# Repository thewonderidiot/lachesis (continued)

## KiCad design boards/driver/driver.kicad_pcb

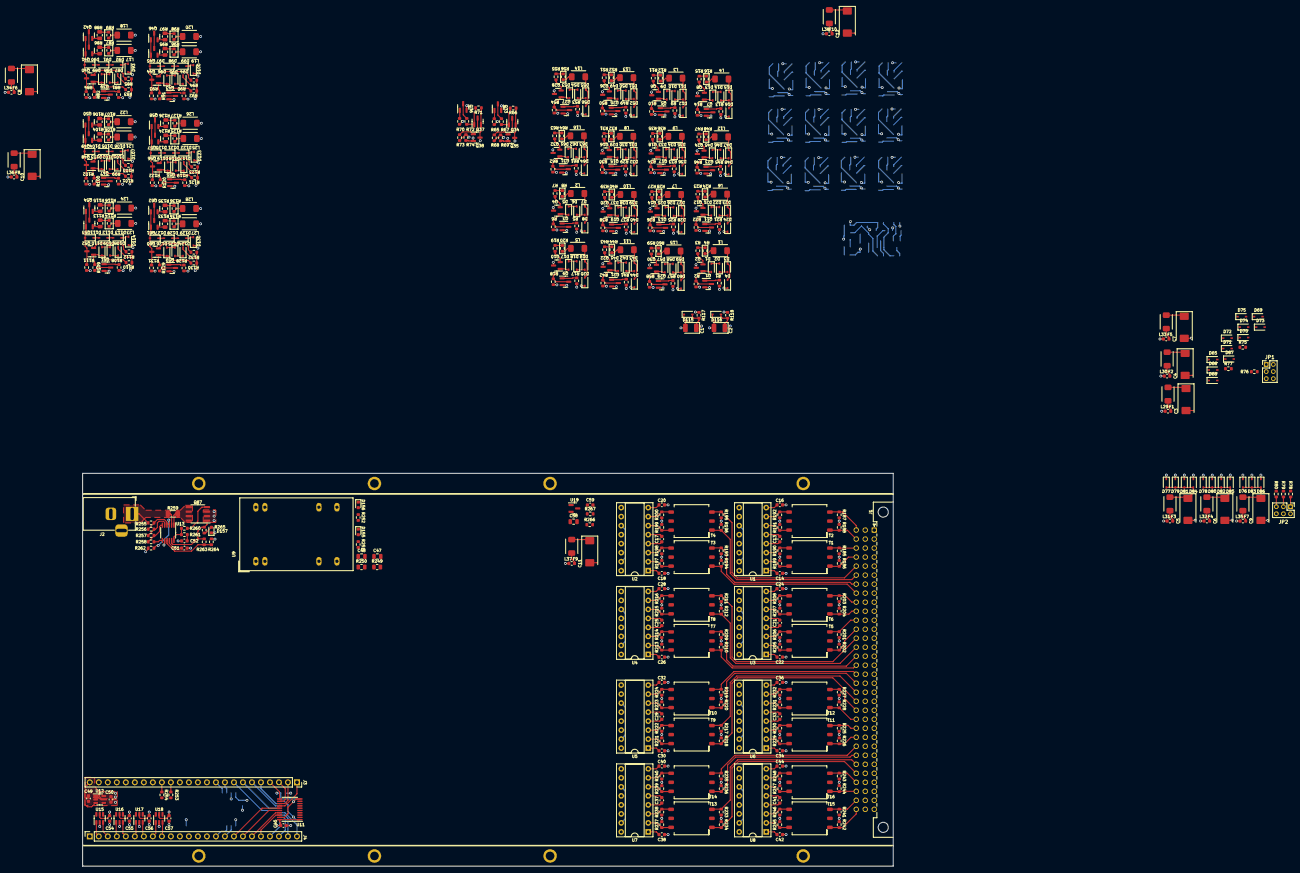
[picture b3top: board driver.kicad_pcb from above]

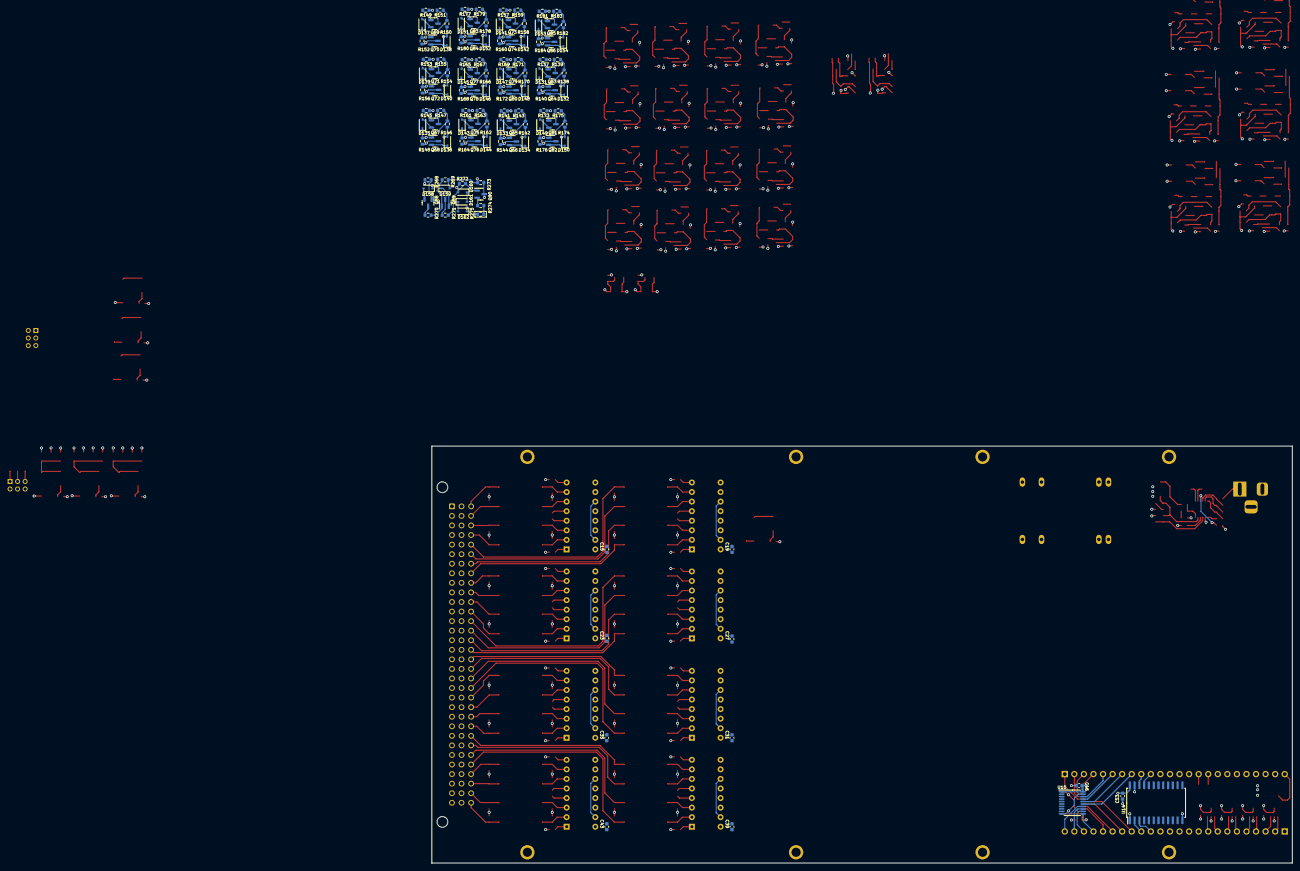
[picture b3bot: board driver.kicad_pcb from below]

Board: 6 copper layers, 228.6 x 110.7 mm, 683 parts (124 on the bottom side), 562 nets.

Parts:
C1, C2: 1.0uF; CP_EIA-3528-21_Kemet-B
C3, C4, C5, C6, C7, C8, C9, C10, C11, C12: 6.8uF; CP_EIA-7343-31_Kemet-D
C13, C15, C16, C17, C19, C20, C21, C23, C24, C25, C27, C28, C29, C31, C32, C33, C35, C36, C37, C39, C40, C41, C43, C44, C52: 0.01uF; C_0603_1608Metric
C14, C18, C22, C26, C30, C34, C38, C42, C51: 100pF; C_0603_1608Metric
C45, C46, C53, C54, C55, C56, C57: 0.1uF; C_0603_1608Metric
C47, C48: 1.0uF; C_0805_2012Metric
C49, C50, C59: 1.0uF; C_0603_1608Metric
C58: 4.7uF; C_0805_2012Metric
D1, D2, D3, D4, D5, D6, D7, D8, D9, D10, D11, D12, D13, D14, D15, D16, D17, D18, D19, D20, D21, D22, D23, D24, D25, D26, D27, D28, D29, D30, D31, D32, D33, D34, D35, D36, D37, D38, D39, D40, D41, D42, D43, D44, D45, D46, D47, D48, D49, D50, D51, D52, D53, D54, D55, D56, D57, D58, D59, D60, D61, D62, D63, D64, D65, D66, D67, D68, D69, D70, D71, D72, D73, D74, D75, D76, D77, D78, D79, D80, D81, D82, D83, D84, D85, D86, D87, D88, D89, D90, D91, D92, D93, D94, D95, D96, D97, D98, D99, D100, D101, D102, D103, D104, D105, D106, D107, D108, D109, D110, D111, D112, D113, D114, D115, D116, D117, D118, D119, D120, D121, D122, D123, D124, D125, D126, D127, D128, D129, D130, D131, D132, D133, D134, D135, D136, D137, D138, D139, D140, D141, D142, D143, D144, D145, D146, D147, D148, D149, D150, D151, D152, D153, D154, D158, D159, D160, D161, D162: 1N4148; D_SOD-323
D155: BLUE; LED_0603_1608Metric
D156: TEAL; LED_0603_1608Metric
D157: ORANGE; LED_0603_1608Metric
F1, F2, F3, F4, F5, F6, F7, F8, F9, F10: 250mA; Fuse_0603_1608Metric
H1, H2, H3, H4, H5, H6, H7, H8: MountingHole_Pad; MountingHole_No2_Pad
J1: DIN41612_03x32_C; DIN41612_C_3x32_Male_Horizontal_THT
J2: Barrel_Jack_Switch; BarrelJack_CUI_PJ-002A
J3, J4: Conn_01x24; PinSocket_1x24_P2.54mm_Vertical
JP1, JP2: Conn_02x03_Odd_Even; PinHeader_2x03_P2.00mm_Vertical
L1, L2, L3, L4, L5, L6, L7, L8, L9, L10, L11, L12, L13, L14, L15, L16: 2.2uH; API_Delevan_1812R
L17, L18, L19, L20, L21, L22, L23, L24, L25, L26, L27, L28: 3.9uH; API_Delevan_1812R
L29, L30, L31, L32, L33, L34, L35, L36, L37, L38: 8.2uH; API_Delevan_1812R
Q1, Q2, Q3, Q4, Q5, Q6, Q7, Q8, Q9, Q10, Q11, Q12, Q13, Q14, Q15, Q16, Q17, Q18, Q19, Q20, Q21, Q22, Q23, Q24, Q25, Q26, Q27, Q28, Q29, Q30, Q31, Q32, Q33, Q35, Q36, Q38, Q39, Q41, Q42, Q43, Q45, Q46, Q47, Q49, Q50, Q51, Q53, Q54, Q55, Q57, Q58, Q59, Q61, Q62, Q63, Q65, Q67, Q69, Q71, Q73, Q75, Q77, Q79, Q81, Q83, Q85, Q88, Q90: MMBT2222; SOT-23
Q34, Q37, Q40, Q44, Q48, Q52, Q56, Q60, Q64, Q66, Q68, Q70, Q72, Q74, Q76, Q78, Q80, Q82, Q84, Q86, Q89: MMBT2907; SOT-23
Q87: IRF7413; SO-8_3.9x4.9mm_P1.27mm
R1, R5, R9, R13, R17, R21, R25, R29, R33, R37, R41, R45, R49, R53, R57, R61, R65, R70, R81, R82, R90, R91, R99, R100, R108, R109, R119, R120, R128, R129, R137, R141, R145, R149, R153, R157, R161, R165, R169, R173, R177, R181, R261, R265, R268: 1k; R_0603_1608Metric
R2, R6, R10, R14, R18, R22, R26, R30, R34, R38, R42, R46, R50, R54, R58, R62: 390; R_0603_1608Metric
R3, R7, R11, R15, R19, R23, R27, R31, R35, R39, R43, R47, R51, R55, R59, R63: 4.7; R_0603_1608Metric
R4, R8, R12, R16, R20, R24, R28, R32, R36, R40, R44, R48, R52, R56, R60, R64, R87, R89, R96, R98, R105, R107, R114, R116, R125, R127, R134, R136, R275: NOM; R_0603_1608Metric
R66, R71: 470; R_0603_1608Metric
R67, R69, R72, R74, R139, R143, R147, R151, R155, R159, R163, R167, R171, R175, R179, R183, R251, R252: 2k; R_0603_1608Metric
R68, R73: 750; R_0603_1608Metric
R75, R76, R77, R78, R79, R80: 200; R_0603_1608Metric
R83, R84, R92, R93, R101, R102, R110, R111, R121, R122, R130, R131, R138, R142, R146, R150, R154, R158, R162, R166, R170, R174, R178, R182, R269, R270, R272: 5.1k; R_0603_1608Metric
R85, R94, R103, R112, R123, R132: 27; R_0603_1608Metric
R86, R88, R95, R97, R104, R106, R113, R115, R124, R126, R133, R135: 7.5; R_0805_2012Metric
R117, R118, R140, R144, R148, R152, R156, R160, R164, R168, R172, R176, R180, R184, R273: 3k; R_0603_1608Metric
R185, R186, R187, R188, R193, R194, R195, R196, R201, R202, R203, R204, R209, R210, R211, R212, R217, R218, R219, R220, R225, R226, R227, R228, R233, R234, R235, R236, R241, R242, R243, R244: 2.7k; R_0603_1608Metric
R189, R190, R191, R192, R197, R198, R199, R200, R205, R206, R207, R208, R213, R214, R215, R216, R221, R222, R223, R224, R229, R230, R231, R232, R237, R238, R239, R240, R245, R246, R247, R248: 100; R_0603_1608Metric
R249, R250: 0; R_0805_2012Metric
R253: 12k; R_0603_1608Metric
R254: 2.4k; R_0603_1608Metric
R255: 1020k; R_0603_1608Metric
R256: 2.87k; R_0603_1608Metric
R257: 9.76k; R_0603_1608Metric
R258: 54.9k; R_0603_1608Metric
R259: 0.025; R_1206_3216Metric
R260, R274: 10; R_0603_1608Metric
R262, R263: 10k; R_0603_1608Metric
R264: 2.5k; R_0603_1608Metric
R266: 1.27k; R_0603_1608Metric
R267: 249; R_0603_1608Metric
R271: 680; R_0603_1608Metric
T1, T2, T3, T4, T5, T6, T7, T8, T9, T10, T11, T12, T13, T14, T15, T16: 1:1; Transformer_Murata_786J
U1, U2, U3, U4, U5, U6, U7, U8: SN7524; DIP-16_W7.62mm_Socket
U9: JTE0624D05; Converter_DCDC_XP_POWER_JTExxxxDxx_THT
U10, U11: 74LVC245; TSSOP-20_4.4x6.5mm_P0.65mm
U12: ADP151-3.3; TSOT-23-5
U13: LTC4231-1; MSOP-12_3x4mm_P0.65mm
U14: 74HC4514; SOIC-24W_7.5x15.4mm_P1.27mm
U15, U16, U17, U18: 74LVC2G04; SOT-23-6
U19: AD1582BRTZ; SOT-23

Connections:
+3V3: C45.2, C46.2, C50.1, C53.2, C54.1, C55.1, C56.1, C57.1, U10.1 (A->B), U10.20 (VCC), U11.1 (A->B), U11.20 (VCC), U12.5 (VOUT), U14.1 (~LE), U14.24 (VCC), U15.5 (VCC), U16.5 (VCC), U17.5 (VCC), U18.5 (VCC)
+5V: C15.1, C19.1, C23.1, C27.1, C31.1, C35.1, C39.1, C43.1, C48.1, C58.2, R249.1, R252.1, R254.2, U1.16 (VCC+), U2.16 (VCC+), U3.16 (VCC+), U4.16 (VCC+), U5.16 (VCC+), U6.16 (VCC+), U7.16 (VCC+), U8.16 (VCC+), U19.3 (VIN)
+14V: F1.2, F2.2, F3.2, F4.2, F5.2, F6.2, F7.2, F8.2, F9.2, F10.2, Q87.1 (S), Q87.2 (S), Q87.3 (S), R117.2, R118.2, R263.1, R265.1, U13.11 (SOURCE)
-5V: C16.2, C20.2, C24.2, C28.2, C32.2, C36.2, C40.2, C44.2, C47.2, R250.1, R251.1, U1.8 (VCC-), U2.8 (VCC-), U3.8 (VCC-), U4.8 (VCC-), U5.8 (VCC-), U6.8 (VCC-), U7.8 (VCC-), U8.8 (VCC-)
/Connector/GAR1: J1.c3, R185.1, T1.3 (P2)
/Connector/GAR2: J1.c5, R195.1, T4.3 (P2)
/Connector/GAR3: J1.c7, R193.1, T3.3 (P2)
/Connector/GAR4: J1.c9, R203.1, T6.3 (P2)
/Connector/GAR5: J1.c11, R201.1, T5.3 (P2)
/Connector/GAR6: J1.c13, R211.1, T8.3 (P2)
/Connector/GAR7: J1.c15, R209.1, T7.3 (P2)
/Connector/GAR8: J1.c17, R219.1, T10.3 (P2)
/Connector/GAR9: J1.c19, R217.1, T9.3 (P2)
/Connector/GAR10: J1.c21, R227.1, T12.3 (P2)
/Connector/GAR11: J1.c23, R225.1, T11.3 (P2)
/Connector/GAR12: J1.c25, R235.1, T14.3 (P2)
/Connector/GAR13: J1.c27, R233.1, T13.3 (P2)
/Connector/GAR14: J1.c29, R243.1, T16.3 (P2)
/Connector/GAR15: J1.c1, R187.1, T2.3 (P2)
/Connector/GAR16: J1.c31, R241.1, T15.3 (P2)
/Connector/GBR1: J1.c4, R186.2, T1.1
/Connector/GBR2: J1.c6, R196.2, T4.1
/Connector/GBR3: J1.c8, R194.2, T3.1
/Connector/GBR4: J1.c10, R204.2, T6.1
/Connector/GBR5: J1.c12, R202.2, T5.1
/Connector/GBR6: J1.c14, R212.2, T8.1
/Connector/GBR7: J1.c16, R210.2, T7.1
/Connector/GBR8: J1.c18, R220.2, T10.1
/Connector/GBR9: J1.c20, R218.2, T9.1
/Connector/GBR10: J1.c22, R228.2, T12.1
/Connector/GBR11: J1.c24, R226.2, T11.1
/Connector/GBR12: J1.c26, R236.2, T14.1
/Connector/GBR13: J1.c28, R234.2, T13.1
/Connector/GBR14: J1.c30, R244.2, T16.1
/Connector/GBR15: J1.c2, R188.2, T2.1
/Connector/GBR16: J1.c32, R242.2, T15.1
/Connector/MODR1: J1.b5, Q90.3 (C), R273.2
/Connector/RCD1: D68.1 (K), J1.b25
/Connector/RCD2: D73.1 (K), J1.b26
/Connector/RCD3: D69.1 (K), J1.b27
/Connector/RCD4: D74.1 (K), J1.b28
/Connector/RCD5: D79.1 (K), J1.b29
/Connector/RCD6: D84.1 (K), J1.b30
/Connector/RCD7: D80.1 (K), J1.b31
/Connector/RCD8: D85.1 (K), J1.b32
/Connector/RFD1: D66.1 (K), J1.a25
/Connector/RFD2: D70.1 (K), J1.a26
/Connector/RFD3: D67.1 (K), J1.a27
/Connector/RFD4: D71.1 (K), J1.a28
/Connector/RFD5: D77.1 (K), J1.a29
/Connector/RFD6: D81.1 (K), J1.a30
/Connector/RFD7: D78.1 (K), J1.a31
/Connector/RFD8: D82.1 (K), J1.a32
/Connector/RSTRD1: D83.1 (K), J1.b1, R79.2
/Connector/RSTRD2: D76.1 (K), J1.b2, R78.2
/Connector/RSTRD3: D72.1 (K), J1.b3, R76.2
/Connector/RSTRD4: D65.1 (K), J1.b4, R75.2
/Connector/SETRN1: D75.1 (K), J1.a23, R77.2
/Connector/SETRN2: D86.1 (K), J1.a24, R80.2
/Connector/STR1: J1.b8, Q64.3 (C), R140.1
/Connector/STR2: J1.b9, Q66.3 (C), R144.1
/Connector/STR3: J1.b10, Q68.3 (C), R148.1
/Connector/STR4: J1.b11, Q70.3 (C), R152.1
/Connector/STR5: J1.b12, Q72.3 (C), R156.1
/Connector/STR6: J1.b13, Q74.3 (C), R160.1
/Connector/STR7: J1.b14, Q76.3 (C), R164.1
/Connector/STR8: J1.b15, Q78.3 (C), R168.1
/Connector/STR9: J1.b16, Q80.3 (C), R172.1
/Connector/STR10: J1.b17, Q82.3 (C), R176.1
/Connector/STR11: J1.b18, Q84.3 (C), R180.1
/Connector/STR12: J1.b19, Q86.3 (C), R184.1
/Connector/XCN1: J1.a15, Q4.3 (C)
/Connector/XCN2: J1.a16, Q8.3 (C)
/Connector/XCN3: J1.a17, Q12.3 (C)
/Connector/XCN4: J1.a18, Q30.3 (C)
/Connector/XCN5: J1.a19, Q20.3 (C)
/Connector/XCN6: J1.a20, Q24.3 (C)
/Connector/XCN7: J1.a21, Q28.3 (C)
/Connector/XCN8: J1.a22, Q32.3 (C)
/Connector/XFN1: J1.a7, Q2.3 (C)
/Connector/XFN2: J1.a8, Q6.3 (C)
/Connector/XFN3: J1.a9, Q10.3 (C)
/Connector/XFN4: J1.a10, Q14.3 (C)
/Connector/XFN5: J1.a11, Q18.3 (C)
/Connector/XFN6: J1.a12, Q22.3 (C)
/Connector/XFN7: J1.a13, Q26.3 (C)
/Connector/XFN8: J1.a14, Q16.3 (C)
/Connector/XRST1: J1.a3, JP2.4, Q45.3 (C), Q46.3 (C)
/Connector/XRST2: J1.a4, JP2.2, Q53.3 (C), Q54.3 (C)
/Connector/XRST3: J1.a5, JP1.4, Q57.3 (C), Q58.3 (C)
/Connector/XRST4: J1.a6, JP1.2, Q61.3 (C), Q62.3 (C)
/Connector/XSET1: J1.a1, JP1.6, Q41.3 (C), Q42.3 (C)
/Connector/XSET2: J1.a2, JP2.6, Q49.3 (C), Q50.3 (C)
/FPGA and Power/5V_FPGA: C49.2, J3.24, U12.1 (VIN), U12.3 (EN)
/FPGA and Power/14V_IN: J2.1, R253.2, R255.2, R259.2, U9.22 (VIN+), U9.23 (VIN+), U13.2 (IN)
/FPGA and Power/14V_SENSE: Q87.5 (D), Q87.6 (D), Q87.7 (D), Q87.8 (D), R259.1, U13.1 (SENSE)
/FPGA and Power/ADC_5V: J3.16, R254.1
/FPGA and Power/ADC_14V: J3.15, R253.1
/FPGA and Power/EN_14V: J3.17, R262.1, U13.3 (~SHDN)
/FPGA and Power/IHENV: J4.14, R65.2, R70.2
/FPGA and Power/IL1: J4.2, R1.2, U15.1
/FPGA and Power/IL2: J4.3, R9.2, U15.3
/FPGA and Power/IL3: J4.4, R17.2, U16.1
/FPGA and Power/IL4: J4.5, R25.2, U16.3
/FPGA and Power/IL5: J4.6, R33.2, U17.1
/FPGA and Power/IL6: J4.7, R41.2, U17.3
/FPGA and Power/IL7: J4.8, R49.2, U18.1
/FPGA and Power/IL8: J4.9, R29.2, U18.3
/FPGA and Power/PG_14V: J3.18, R263.2, R264.1, U13.9 (STATUS)
/FPGA and Power/RESET1: J4.12, R90.2
/FPGA and Power/RESET2: J3.11, R108.2
/FPGA and Power/RESET3: J3.12, R119.2
/FPGA and Power/RESET4: J4.11, R128.2
/FPGA and Power/ROPER: J3.13, R268.2
/FPGA and Power/SA1: U1.12, U10.2 (A0)
/FPGA and Power/SA2: U2.14, U10.3 (A1)
/FPGA and Power/SA3: U2.12, U10.4 (A2)
/FPGA and Power/SA4: U3.14, U10.5 (A3)
/FPGA and Power/SA5: U3.12, U10.6 (A4)
/FPGA and Power/SA6: U4.14, U10.7 (A5)
/FPGA and Power/SA7: U4.12, U10.8 (A6)
/FPGA and Power/SA8: U5.14, U10.9 (A7)
/FPGA and Power/SA9: U5.12, U11.2 (A0)
/FPGA and Power/SA10: U6.14, U11.3 (A1)
/FPGA and Power/SA11: U6.12, U11.4 (A2)
/FPGA and Power/SA12: U7.14, U11.5 (A3)
/FPGA and Power/SA13: U7.12, U11.6 (A4)
/FPGA and Power/SA14: U8.14, U11.7 (A5)
/FPGA and Power/SA15: U1.14, U11.8 (A6)
/FPGA and Power/SA16: U8.12, U11.9 (A7)
/FPGA and Power/SAF1: J3.5, U10.18 (B0)
/FPGA and Power/SAF2: J3.6, U10.17 (B1)
/FPGA and Power/SAF3: J3.7, U10.16 (B2)
/FPGA and Power/SAF4: J3.8, U10.15 (B3)
/FPGA and Power/SAF5: J4.24, U10.14 (B4)
/FPGA and Power/SAF6: J4.23, U10.13 (B5)
/FPGA and Power/SAF7: J4.22, U10.12 (B6)
/FPGA and Power/SAF8: J4.21, U10.11 (B7)
/FPGA and Power/SAF9: J4.20, U11.18 (B0)
/FPGA and Power/SAF10: J4.19, U11.17 (B1)
/FPGA and Power/SAF11: J4.18, U11.16 (B2)
/FPGA and Power/SAF12: J4.17, U11.15 (B3)
/FPGA and Power/SAF13: J3.1, U11.14 (B4)
/FPGA and Power/SAF14: J3.2, U11.13 (B5)
/FPGA and Power/SAF15: J3.3, U11.12 (B6)
/FPGA and Power/SAF16: J3.4, U11.11 (B7)
/FPGA and Power/SBF: J3.19, U1.11, U1.15, U2.11, U2.15, U3.11, U3.15, U4.11, U4.15, U5.11, U5.15, U6.11, U6.15, U7.11, U7.15, U8.11, U8.15
/FPGA and Power/SE1: R137.2, U14.9 (Y1)
/FPGA and Power/SE2: R141.2, U14.10 (Y2)
/FPGA and Power/SE3: R145.2, U14.8 (Y3)
/FPGA and Power/SE4: R149.2, U14.7 (Y4)
/FPGA and Power/SE5: R153.2, U14.6 (Y5)
/FPGA and Power/SE6: R157.2, U14.5 (Y6)
/FPGA and Power/SE7: R161.2, U14.4 (Y7)
/FPGA and Power/SE8: R165.2, U14.18 (Y8)
/FPGA and Power/SE9: R169.2, U14.17 (Y9)
/FPGA and Power/SE10: R173.2, U14.20 (Y10)
/FPGA and Power/SE11: R177.2, U14.19 (Y11)
/FPGA and Power/SE12: R181.2, U14.14 (Y12)
/FPGA and Power/SET1: J3.14, R81.2
/FPGA and Power/SET2: J4.13, R99.2
/FPGA and Power/STRA0: J4.16, U14.2 (A0)
/FPGA and Power/STRA1: J4.15, U14.3 (A1)
/FPGA and Power/STRA2: J3.10, U14.21 (A2)
/FPGA and Power/STRA3: J3.9, U14.22 (A3)
/FPGA and Power/~IL1: R5.2, U15.6
/FPGA and Power/~IL2: R13.2, U15.4
/FPGA and Power/~IL3: R21.2, U16.6
/FPGA and Power/~IL4: R57.2, U16.4
/FPGA and Power/~IL5: R37.2, U17.6
/FPGA and Power/~IL6: R45.2, U17.4
/FPGA and Power/~IL7: R53.2, U18.6
/FPGA and Power/~IL8: R61.2, U18.4
/Rope Drivers/40331A: Q35.2 (E), R2.1, R6.1, R10.1, R14.1, R18.1, R22.1, R26.1, R30.1, R69.1
/Rope Drivers/40332A: Q38.2 (E), R34.1, R38.1, R42.1, R46.1, R50.1, R54.1, R58.1, R62.1, R74.1
/Rope Drivers/40365A: C1.1, D115.2 (A), Q1.2 (E), Q3.2 (E), Q5.2 (E), Q7.2 (E), Q9.2 (E), Q11.2 (E), Q13.2 (E), Q15.2 (E), Q33.2 (E), Q39.2 (E), Q43.2 (E), Q55.2 (E), R117.1
/Rope Drivers/40366A: C2.1, D116.2 (A), Q17.2 (E), Q19.2 (E), Q21.2 (E), Q23.2 (E), Q25.2 (E), Q27.2 (E), Q29.2 (E), Q31.2 (E), Q36.2 (E), Q47.2 (E), Q51.2 (E), Q59.2 (E), R118.1
/Rope Drivers/BPLIZ1: C8.1, D87.2 (A), D94.2 (A), D117.2 (A), L34.2, Q34.2 (E), Q35.3 (C), R66.1, R83.1, R85.1, R92.1, R94.1, R121.1, R123.1
/Rope Drivers/BPLIZ2: C10.1, D101.2 (A), D108.2 (A), D124.2 (A), L36.2, Q37.2 (E), Q38.3 (C), R71.1, R101.1, R103.1, R110.1, R112.1, R130.1, R132.1
/Rope Drivers/BPLMX1: C3.1, D66.2 (A), D68.2 (A), D70.2 (A), D73.2 (A), L29.2
/Rope Drivers/BPLMX2: C4.1, D67.2 (A), D69.2 (A), D71.2 (A), D74.2 (A), L30.2
/Rope Drivers/BPLMX3: C7.1, D65.2 (A), D72.2 (A), D75.2 (A), L33.2
/Rope Drivers/BPLMY1: C5.1, D77.2 (A), D79.2 (A), D81.2 (A), D84.2 (A), L31.2
/Rope Drivers/BPLMY2: C6.1, D78.2 (A), D80.2 (A), D82.2 (A), D85.2 (A), L32.2
/Rope Drivers/BPLMY3: C9.1, D76.2 (A), D83.2 (A), D86.2 (A), L35.2
/Sense Amplifiers/BPLSWX: C11.1, L37.2, R185.2, R186.1, R187.2, R188.1, R193.2, R194.1, R195.2, R196.1, R201.2, R202.1, R203.2, R204.1, R209.2, R210.1, R211.2, R212.1, R217.2, R218.1, R219.2, R220.1, R225.2, R226.1, R227.2, R228.1, R233.2, R234.1, R235.2, R236.1, R241.2, R242.1, R243.2, R244.1
/Sense Amplifiers/VREF: C13.2, C17.2, C21.2, C25.2, C29.2, C33.2, C37.2, C41.2, R266.2, R267.1, U1.5 (+), U2.5 (+), U3.5 (+), U4.5 (+), U5.5 (+), U6.5 (+), U7.5 (+), U8.5 (+)
/Strand Select/BPLSWZ: C12.1, D132.2 (A), D134.2 (A), D136.2 (A), D138.2 (A), D140.2 (A), D142.2 (A), D144.2 (A), D146.2 (A), D148.2 (A), D150.2 (A), D152.2 (A), D154.2 (A), D159.2 (A), L38.2, R138.1, R142.1, R146.1, R150.1, R154.1, R158.1, R162.1, R166.1, R170.1, R174.1, R178.1, R182.1, R269.1, R273.1
/Strand Select/RPR: Q88.3 (C), R270.2
GND: C1.2, C2.2, C3.2, C4.2, C5.2, C6.2, C7.2, C8.2, C9.2, C10.2, C11.2, C12.2, C13.1, C14.1, C15.2, C16.1, C17.1, C18.1, C19.2, C20.1, C21.1, C22.1, C23.2, C24.1, C25.1, C26.1, C27.2, C28.1, C29.1, C30.1, C31.2, C32.1, C33.1, C34.1, C35.2, C36.1, C37.1, C38.1, C39.2, C40.1, C41.1, C42.1, C43.2, C44.1, C45.1, C46.1, C47.1, C48.2, C49.1, C50.2, C51.2, C52.2, C53.1, C54.2, C55.2, C56.2, C57.2, C58.1, C59.2, D4.1 (K), D8.1 (K), D12.1 (K), D16.1 (K), D20.1 (K), D24.1 (K), D28.1 (K), D32.1 (K), D36.1 (K), D40.1 (K), D44.1 (K), D48.1 (K), D52.1 (K), D56.1 (K), D60.1 (K), D64.1 (K), D93.1 (K), D100.1 (K), D107.1 (K), D114.1 (K), D115.1 (K), D116.1 (K), D123.1 (K), D130.1 (K), D131.1 (K), D133.1 (K), D135.1 (K), D137.1 (K), D139.1 (K), D141.1 (K), D143.1 (K), D145.1 (K), D147.1 (K), D149.1 (K), D151.1 (K), D153.1 (K), D155.2 (A), D156.1 (K), D157.1 (K), D158.1 (K), D162.1 (K), H1.1, H2.1, H3.1, H4.1, H5.1, H6.1, H7.1, H8.1, J1.b20, J1.b21, J1.b22, J1.b23, J1.b24, J2.2, J2.3, J4.1, L17.2, L18.2, L19.2, L20.2, L21.2, L22.2, L23.2, L24.2, L25.2, L26.2, L27.2, L28.2, R68.2, R69.2, R73.2, R74.2, R84.2, R93.2, R102.2, R111.2, R122.2, R131.2, R140.2, R144.2, R148.2, R152.2, R156.2, R160.2, R164.2, R168.2, R172.2, R176.2, R180.2, R184.2, R189.2, R190.1, R191.2, R192.1, R197.2, R198.1, R199.2, R200.1, R205.2, R206.1, R207.2, R208.1, R213.2, R214.1, R215.2, R216.1, R221.2, R222.1, R223.2, R224.1, R229.2, R230.1, R231.2, R232.1, R237.2, R238.1, R239.2, R240.1, R245.2, R246.1, R247.2, R248.1, R262.2, R264.2, R267.2, R272.2, R275.2, U1.4 (-), U1.9 (GND), U1.13 (GND), U2.4 (-), U2.9 (GND), U2.13 (GND), U3.4 (-), U3.9 (GND), U3.13 (GND), U4.4 (-), U4.9 (GND), U4.13 (GND), U5.4 (-), U5.9 (GND), U5.13 (GND), U6.4 (-), U6.9 (GND), U6.13 (GND), U7.4 (-), U7.9 (GND), U7.13 (GND), U8.4 (-), U8.9 (GND), U8.13 (GND), U9.2 (VIN-), U9.3 (VIN-), U9.9 (COM), U9.16 (COM), U10.10 (GND), U10.19 (CE), U11.10 (GND), U11.19 (CE), U12.2 (GND), U13.8 (GND), U14.12 (GND), U14.23 (~E), U15.2 (GND), U16.2 (GND), U17.2 (GND), U18.2 (GND), U19.2 (GND)
unnamed: C14.2, U1.1 (CEXT)
unnamed: C18.2, U2.1 (CEXT)
unnamed: C22.2, U3.1 (CEXT)
unnamed: C26.2, U4.1 (CEXT)
unnamed: C30.2, U5.1 (CEXT)
unnamed: C34.2, U6.1 (CEXT)
unnamed: C38.2, U7.1 (CEXT)
unnamed: C42.2, U8.1 (CEXT)
unnamed: C51.1, U13.10 (TIMER)
unnamed: C52.1, R261.1
unnamed: C59.1, R266.1, U19.1 (VOUT)
unnamed: D1.1 (K), D2.2 (A)
unnamed: D1.2 (A), Q1.3 (C), Q2.1 (B), R2.2
unnamed: D2.1 (K), D3.2 (A)
unnamed: D3.1 (K), D4.2 (A), L1.2
unnamed: D5.1 (K), D6.2 (A)
unnamed: D5.2 (A), Q3.3 (C), Q4.1 (B), R6.2
unnamed: D6.1 (K), D7.2 (A)
unnamed: D7.1 (K), D8.2 (A), L2.2
unnamed: D9.2 (A), Q5.3 (C), Q6.1 (B), R10.2
unnamed: D10.1 (K), D11.2 (A)
unnamed: D9.1 (K), D10.2 (A)
unnamed: D11.1 (K), D12.2 (A), L3.2
unnamed: D13.1 (K), D14.2 (A)
unnamed: D13.2 (A), Q7.3 (C), Q8.1 (B), R14.2
unnamed: D14.1 (K), D15.2 (A)
unnamed: D15.1 (K), D16.2 (A), L4.2
unnamed: D17.1 (K), D18.2 (A)
unnamed: D17.2 (A), Q9.3 (C), Q10.1 (B), R18.2
unnamed: D18.1 (K), D19.2 (A)
unnamed: D19.1 (K), D20.2 (A), L5.2
unnamed: D21.1 (K), D22.2 (A)
unnamed: D21.2 (A), Q11.3 (C), Q12.1 (B), R22.2
unnamed: D22.1 (K), D23.2 (A)
unnamed: D23.1 (K), D24.2 (A), L6.2
unnamed: D25.1 (K), D26.2 (A)
unnamed: D25.2 (A), Q13.3 (C), Q14.1 (B), R26.2
unnamed: D26.1 (K), D27.2 (A)
unnamed: D27.1 (K), D28.2 (A), L7.2
unnamed: D29.1 (K), D30.2 (A)
unnamed: D29.2 (A), Q15.3 (C), Q16.1 (B), R30.2
unnamed: D30.1 (K), D31.2 (A)
unnamed: D31.1 (K), D32.2 (A), L8.2
unnamed: D33.1 (K), D34.2 (A)
unnamed: D33.2 (A), Q17.3 (C), Q18.1 (B), R34.2
unnamed: D34.1 (K), D35.2 (A)
unnamed: D35.1 (K), D36.2 (A), L9.2
unnamed: D37.1 (K), D38.2 (A)
unnamed: D37.2 (A), Q19.3 (C), Q20.1 (B), R38.2
unnamed: D38.1 (K), D39.2 (A)
unnamed: D39.1 (K), D40.2 (A), L10.2
unnamed: D41.1 (K), D42.2 (A)
unnamed: D41.2 (A), Q21.3 (C), Q22.1 (B), R42.2
unnamed: D42.1 (K), D43.2 (A)
unnamed: D43.1 (K), D44.2 (A), L11.2
unnamed: D45.1 (K), D46.2 (A)
unnamed: D45.2 (A), Q23.3 (C), Q24.1 (B), R46.2
unnamed: D46.1 (K), D47.2 (A)
unnamed: D47.1 (K), D48.2 (A), L12.2
unnamed: D49.1 (K), D50.2 (A)
unnamed: D49.2 (A), Q25.3 (C), Q26.1 (B), R50.2
unnamed: D50.1 (K), D51.2 (A)
unnamed: D51.1 (K), D52.2 (A), L13.2
unnamed: D53.1 (K), D54.2 (A)
unnamed: D53.2 (A), Q27.3 (C), Q28.1 (B), R54.2
unnamed: D54.1 (K), D55.2 (A)
unnamed: D55.1 (K), D56.2 (A), L14.2
unnamed: D57.1 (K), D58.2 (A)
unnamed: D57.2 (A), Q29.3 (C), Q30.1 (B), R58.2
unnamed: D58.1 (K), D59.2 (A)
unnamed: D59.1 (K), D60.2 (A), L15.2
unnamed: D61.1 (K), D62.2 (A)
unnamed: D61.2 (A), Q31.3 (C), Q32.1 (B), R62.2
unnamed: D62.1 (K), D63.2 (A)
unnamed: D63.1 (K), D64.2 (A), L16.2
unnamed: D87.1 (K), D88.2 (A)
unnamed: D88.1 (K), D89.2 (A)
unnamed: D89.1 (K), Q40.1 (B), R82.1, R83.2
unnamed: D90.1 (K), D91.2 (A)
unnamed: D90.2 (A), Q40.3 (C), Q41.1 (B), Q42.1 (B), R84.1
unnamed: D91.1 (K), D92.2 (A)
unnamed: D92.1 (K), D93.2 (A)
unnamed: D94.1 (K), D95.2 (A)
unnamed: D95.1 (K), D96.2 (A)
unnamed: D96.1 (K), Q44.1 (B), R91.1, R92.2
unnamed: D97.1 (K), D98.2 (A)
unnamed: D97.2 (A), Q44.3 (C), Q45.1 (B), Q46.1 (B), R93.1
unnamed: D98.1 (K), D99.2 (A)
unnamed: D99.1 (K), D100.2 (A)
unnamed: D101.1 (K), D102.2 (A)
unnamed: D102.1 (K), D103.2 (A)
unnamed: D103.1 (K), Q48.1 (B), R100.1, R101.2
unnamed: D104.1 (K), D105.2 (A)
unnamed: D104.2 (A), Q48.3 (C), Q49.1 (B), Q50.1 (B), R102.1
unnamed: D105.1 (K), D106.2 (A)
unnamed: D106.1 (K), D107.2 (A)
unnamed: D108.1 (K), D109.2 (A)
unnamed: D109.1 (K), D110.2 (A)
unnamed: D110.1 (K), Q52.1 (B), R109.1, R110.2
unnamed: D111.1 (K), D112.2 (A)
unnamed: D111.2 (A), Q52.3 (C), Q53.1 (B), Q54.1 (B), R111.1
unnamed: D112.1 (K), D113.2 (A)
unnamed: D113.1 (K), D114.2 (A)
unnamed: D117.1 (K), D118.2 (A)
unnamed: D118.1 (K), D119.2 (A)
unnamed: D119.1 (K), Q56.1 (B), R120.1, R121.2
unnamed: D120.1 (K), D121.2 (A)
unnamed: D120.2 (A), Q56.3 (C), Q57.1 (B), Q58.1 (B), R122.1
unnamed: D121.1 (K), D122.2 (A)
unnamed: D122.1 (K), D123.2 (A)
unnamed: D124.1 (K), D125.2 (A)
unnamed: D125.1 (K), D126.2 (A)
unnamed: D126.1 (K), Q60.1 (B), R129.1, R130.2
unnamed: D127.1 (K), D128.2 (A)
unnamed: D127.2 (A), Q60.3 (C), Q61.1 (B), Q62.1 (B), R131.1
unnamed: D128.1 (K), D129.2 (A)
unnamed: D129.1 (K), D130.2 (A)
unnamed: D131.2 (A), Q63.2 (E)
unnamed: D132.1 (K), Q64.2 (E)
unnamed: D133.2 (A), Q65.2 (E)
unnamed: D134.1 (K), Q66.2 (E)
unnamed: D135.2 (A), Q67.2 (E)
unnamed: D136.1 (K), Q68.2 (E)
unnamed: D137.2 (A), Q69.2 (E)
unnamed: D138.1 (K), Q70.2 (E)
unnamed: D139.2 (A), Q71.2 (E)
unnamed: D140.1 (K), Q72.2 (E)
unnamed: D141.2 (A), Q73.2 (E)
unnamed: D142.1 (K), Q74.2 (E)
unnamed: D143.2 (A), Q75.2 (E)
unnamed: D144.1 (K), Q76.2 (E)
unnamed: D145.2 (A), Q77.2 (E)
unnamed: D146.1 (K), Q78.2 (E)
unnamed: D147.2 (A), Q79.2 (E)
unnamed: D148.1 (K), Q80.2 (E)
unnamed: D149.2 (A), Q81.2 (E)
unnamed: D150.1 (K), Q82.2 (E)
unnamed: D151.2 (A), Q83.2 (E)
unnamed: D152.1 (K), Q84.2 (E)
unnamed: D153.2 (A), Q85.2 (E)
unnamed: D154.1 (K), Q86.2 (E)
unnamed: D155.1 (K), R251.2
unnamed: D156.2 (A), R252.2
unnamed: D157.2 (A), R265.2
unnamed: D158.2 (A), Q88.2 (E)
unnamed: D159.1 (K), Q89.2 (E)
unnamed: D160.1 (K), D161.2 (A)
unnamed: D160.2 (A), Q90.1 (B), R271.2, R272.1
unnamed: D161.1 (K), D162.2 (A)
unnamed: F1.1, L29.1
unnamed: F2.1, L30.1
unnamed: F3.1, L31.1
unnamed: F4.1, L32.1
unnamed: F5.1, L33.1
unnamed: F6.1, L34.1
unnamed: F7.1, L35.1
unnamed: F8.1, L36.1
unnamed: F9.1, L37.1
unnamed: F10.1, L38.1
unnamed: JP1.1, R75.1
unnamed: JP1.3, R76.1
unnamed: JP1.5, R77.1
unnamed: JP2.1, R78.1
unnamed: JP2.3, R79.1
unnamed: JP2.5, R80.1
unnamed: L1.1, R4.2
unnamed: L2.1, R8.2
unnamed: L3.1, R12.2
unnamed: L4.1, R16.2
unnamed: L5.1, R20.2
unnamed: L6.1, R24.2
unnamed: L7.1, R28.2
unnamed: L8.1, R32.2
unnamed: L9.1, R36.2
unnamed: L10.1, R40.2
unnamed: L11.1, R44.2
unnamed: L12.1, R48.2
unnamed: L13.1, R52.2
unnamed: L14.1, R56.2
unnamed: L15.1, R60.2
unnamed: L16.1, R64.2
unnamed: L17.1, R87.2
unnamed: L18.1, R89.2
unnamed: L19.1, R96.2
unnamed: L20.1, R98.2
unnamed: L21.1, R105.2
unnamed: L22.1, R107.2
unnamed: L23.1, R114.2
unnamed: L24.1, R116.2
unnamed: L25.1, R125.2
unnamed: L26.1, R127.2
unnamed: L27.1, R134.2
unnamed: L28.1, R136.2
unnamed: Q1.1 (B), R1.1
unnamed: Q2.2 (E), R3.1
unnamed: Q3.1 (B), R5.1
unnamed: Q4.2 (E), R7.1
unnamed: Q5.1 (B), R9.1
unnamed: Q6.2 (E), R11.1
unnamed: Q7.1 (B), R13.1
unnamed: Q8.2 (E), R15.1
unnamed: Q9.1 (B), R17.1
unnamed: Q10.2 (E), R19.1
unnamed: Q11.1 (B), R21.1
unnamed: Q12.2 (E), R23.1
unnamed: Q13.1 (B), R25.1
unnamed: Q14.2 (E), R27.1
unnamed: Q15.1 (B), R29.1
unnamed: Q16.2 (E), R31.1
unnamed: Q17.1 (B), R33.1
unnamed: Q18.2 (E), R35.1
unnamed: Q19.1 (B), R37.1
unnamed: Q20.2 (E), R39.1
unnamed: Q21.1 (B), R41.1
unnamed: Q22.2 (E), R43.1
unnamed: Q23.1 (B), R45.1
unnamed: Q24.2 (E), R47.1
unnamed: Q25.1 (B), R49.1
unnamed: Q26.2 (E), R51.1
unnamed: Q27.1 (B), R53.1
unnamed: Q28.2 (E), R55.1
unnamed: Q29.1 (B), R57.1
unnamed: Q30.2 (E), R59.1
unnamed: Q31.1 (B), R61.1
unnamed: Q32.2 (E), R63.1
unnamed: Q33.1 (B), R65.1
unnamed: Q33.3 (C), R67.2
unnamed: Q34.1 (B), R66.2, R67.1
unnamed: Q34.3 (C), Q35.1 (B), R68.1
unnamed: Q36.1 (B), R70.1
unnamed: Q36.3 (C), R72.2
unnamed: Q37.1 (B), R71.2, R72.1
unnamed: Q37.3 (C), Q38.1 (B), R73.1
unnamed: Q39.1 (B), R81.1
unnamed: Q39.3 (C), R82.2
unnamed: Q40.2 (E), R85.2
unnamed: Q41.2 (E), R86.1
unnamed: Q42.2 (E), R88.1
unnamed: Q43.1 (B), R90.1
unnamed: Q43.3 (C), R91.2
unnamed: Q44.2 (E), R94.2
unnamed: Q45.2 (E), R95.1
unnamed: Q46.2 (E), R97.1
unnamed: Q47.1 (B), R99.1
unnamed: Q47.3 (C), R100.2
unnamed: Q48.2 (E), R103.2
unnamed: Q49.2 (E), R104.1
unnamed: Q50.2 (E), R106.1
unnamed: Q51.1 (B), R108.1
unnamed: Q51.3 (C), R109.2
unnamed: Q52.2 (E), R112.2
unnamed: Q53.2 (E), R113.1
unnamed: Q54.2 (E), R115.1
unnamed: Q55.1 (B), R119.1
unnamed: Q55.3 (C), R120.2
unnamed: Q56.2 (E), R123.2
unnamed: Q57.2 (E), R124.1
unnamed: Q58.2 (E), R126.1
unnamed: Q59.1 (B), R128.1
unnamed: Q59.3 (C), R129.2
unnamed: Q60.2 (E), R132.2
unnamed: Q61.2 (E), R133.1
unnamed: Q62.2 (E), R135.1
unnamed: Q63.1 (B), R137.1
unnamed: Q63.3 (C), R139.2
unnamed: Q64.1 (B), R138.2, R139.1
unnamed: Q65.1 (B), R141.1
unnamed: Q65.3 (C), R143.2
unnamed: Q66.1 (B), R142.2, R143.1
unnamed: Q67.1 (B), R145.1
unnamed: Q67.3 (C), R147.2
unnamed: Q68.1 (B), R146.2, R147.1
unnamed: Q69.1 (B), R149.1
unnamed: Q69.3 (C), R151.2
unnamed: Q70.1 (B), R150.2, R151.1
unnamed: Q71.1 (B), R153.1
unnamed: Q71.3 (C), R155.2
unnamed: Q72.1 (B), R154.2, R155.1
unnamed: Q73.1 (B), R157.1
unnamed: Q73.3 (C), R159.2
unnamed: Q74.1 (B), R158.2, R159.1
unnamed: Q75.1 (B), R161.1
unnamed: Q75.3 (C), R163.2
unnamed: Q76.1 (B), R162.2, R163.1
unnamed: Q77.1 (B), R165.1
unnamed: Q77.3 (C), R167.2
unnamed: Q78.1 (B), R166.2, R167.1
unnamed: Q79.1 (B), R169.1
unnamed: Q79.3 (C), R171.2
unnamed: Q80.1 (B), R170.2, R171.1
unnamed: Q81.1 (B), R173.1
unnamed: Q81.3 (C), R175.2
unnamed: Q82.1 (B), R174.2, R175.1
unnamed: Q83.1 (B), R177.1
unnamed: Q83.3 (C), R179.2
unnamed: Q84.1 (B), R178.2, R179.1
unnamed: Q85.1 (B), R181.1
unnamed: Q85.3 (C), R183.2
unnamed: Q86.1 (B), R182.2, R183.1
unnamed: Q87.4 (G), R260.1
unnamed: Q88.1 (B), R268.1
unnamed: Q89.1 (B), R269.2, R270.1
unnamed: Q89.3 (C), R271.1
unnamed: Q90.2 (E), R274.1
unnamed: R3.2, R4.1
unnamed: R7.2, R8.1
unnamed: R11.2, R12.1
unnamed: R15.2, R16.1
unnamed: R19.2, R20.1
unnamed: R23.2, R24.1
unnamed: R27.2, R28.1
unnamed: R31.2, R32.1
unnamed: R35.2, R36.1
unnamed: R39.2, R40.1
unnamed: R43.2, R44.1
unnamed: R47.2, R48.1
unnamed: R51.2, R52.1
unnamed: R55.2, R56.1
unnamed: R59.2, R60.1
unnamed: R63.2, R64.1
unnamed: R86.2, R87.1
unnamed: R88.2, R89.1
unnamed: R95.2, R96.1
unnamed: R97.2, R98.1
unnamed: R104.2, R105.1
unnamed: R106.2, R107.1
unnamed: R113.2, R114.1
unnamed: R115.2, R116.1
unnamed: R124.2, R125.1
unnamed: R126.2, R127.1
unnamed: R133.2, R134.1
unnamed: R135.2, R136.1
unnamed: R189.1, T1.4 (S2), U1.2
unnamed: R190.2, T1.6 (S1), U1.3
unnamed: R191.1, T2.4 (S2), U1.6
unnamed: R192.2, T2.6 (S1), U1.7
unnamed: R197.1, T3.4 (S2), U2.2
unnamed: R198.2, T3.6 (S1), U2.3
unnamed: R199.1, T4.4 (S2), U2.6
unnamed: R200.2, T4.6 (S1), U2.7
unnamed: R205.1, T5.4 (S2), U3.2
unnamed: R206.2, T5.6 (S1), U3.3
unnamed: R207.1, T6.4 (S2), U3.6
unnamed: R208.2, T6.6 (S1), U3.7
unnamed: R213.1, T7.4 (S2), U4.2
unnamed: R214.2, T7.6 (S1), U4.3
unnamed: R215.1, T8.4 (S2), U4.6
unnamed: R216.2, T8.6 (S1), U4.7
unnamed: R221.1, T9.4 (S2), U5.2
unnamed: R222.2, T9.6 (S1), U5.3
unnamed: R223.1, T10.4 (S2), U5.6
unnamed: R224.2, T10.6 (S1), U5.7
unnamed: R229.1, T11.4 (S2), U6.2
unnamed: R230.2, T11.6 (S1), U6.3
unnamed: R231.1, T12.4 (S2), U6.6
unnamed: R232.2, T12.6 (S1), U6.7
unnamed: R237.1, T13.4 (S2), U7.2
unnamed: R238.2, T13.6 (S1), U7.3
unnamed: R239.1, T14.4 (S2), U7.6
unnamed: R240.2, T14.6 (S1), U7.7
unnamed: R245.1, T15.4 (S2), U8.2
unnamed: R246.2, T15.6 (S1), U8.3
unnamed: R247.1, T16.4 (S2), U8.6
unnamed: R248.2, T16.6 (S1), U8.7
unnamed: R249.2, U9.14 (VOUT+)
unnamed: R250.2, U9.11 (VOUT-)
unnamed: R255.1, R256.2, U13.4 (UVL)
unnamed: R256.1, R257.2, U13.5 (UVH)
unnamed: R257.1, R258.2, U13.6 (OV)
unnamed: R258.1, U13.7 (GNDSW)
unnamed: R260.2, R261.2, U13.12 (GATE)
unnamed: R274.2, R275.1

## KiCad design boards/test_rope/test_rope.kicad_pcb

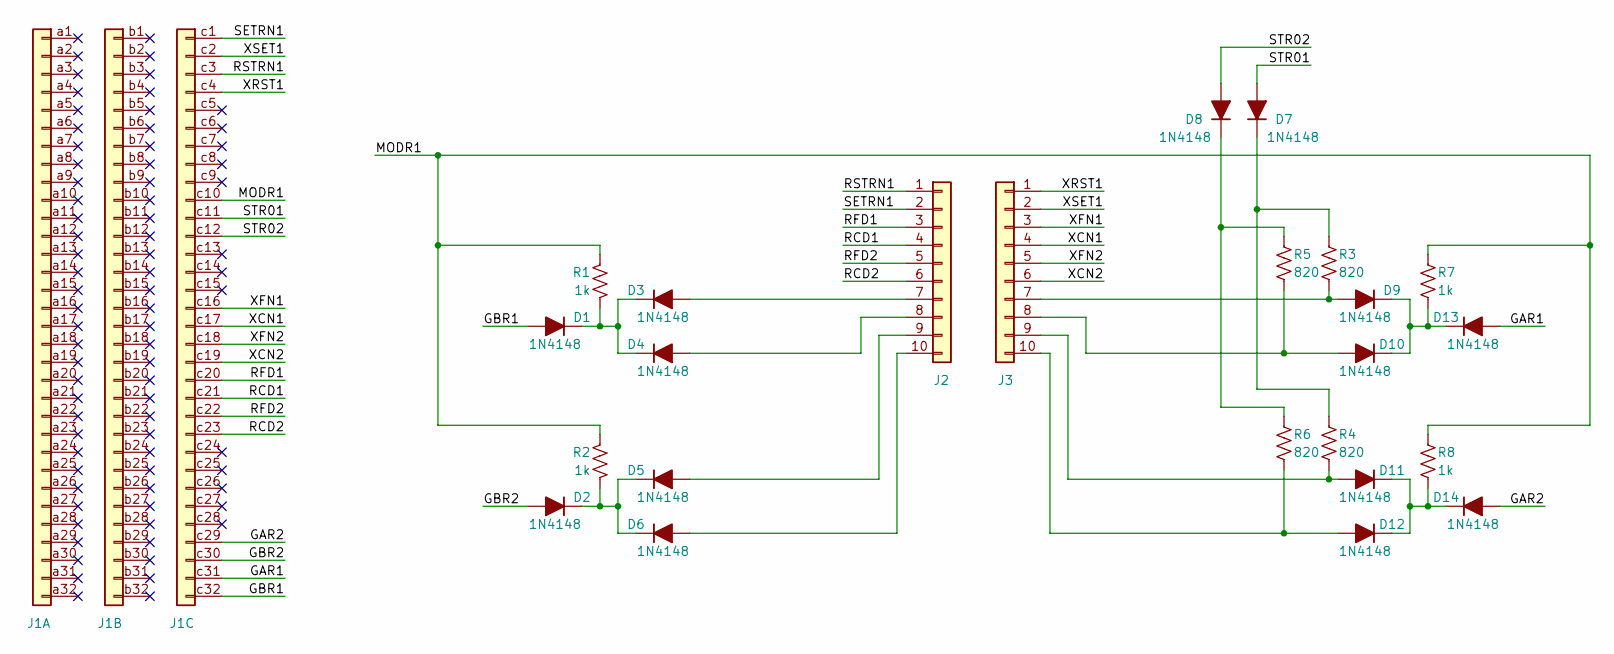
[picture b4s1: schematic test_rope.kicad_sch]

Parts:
D1, D2, D3, D4, D5, D6, D7, D8, D9, D10, D11, D12, D13, D14: 1N4148; D_SOD-323
J1: DIN41612_03x32_C; DIN41612_C_3x32_Female_Vertical_THT
J2, J3: Conn_01x10; PinHeader_1x10_P2.54mm_Vertical
R1, R2, R7, R8: 1k; R_0603_1608Metric
R3, R4, R5, R6: 820; R_0603_1608Metric

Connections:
/GAR1: D13.2 (A), J1.c31
/GAR2: D14.2 (A), J1.c29
/GBR1: D1.2 (A), J1.c32
/GBR2: D2.2 (A), J1.c30
/MODR1: J1.c10, R1.1, R2.1, R7.1, R8.1
/RCD1: J1.c21, J2.4
/RCD2: J1.c23, J2.6
/RFD1: J1.c20, J2.3
/RFD2: J1.c22, J2.5
/RSTRN1: J1.c3, J2.1
/SETRN1: J1.c1, J2.2
/STR01: D7.2 (A), J1.c11
/STR02: D8.2 (A), J1.c12
/XCN1: J1.c17, J3.4
/XCN2: J1.c19, J3.6
/XFN1: J1.c16, J3.3
/XFN2: J1.c18, J3.5
/XRST1: J1.c4, J3.1
/XSET1: J1.c2, J3.2
unnamed: D1.1 (K), D3.1 (K), D4.1 (K), R1.2
unnamed: D2.1 (K), D5.1 (K), D6.1 (K), R2.2
unnamed: D3.2 (A), J2.7
unnamed: D4.2 (A), J2.8
unnamed: D5.2 (A), J2.9
unnamed: D6.2 (A), J2.10
unnamed: D7.1 (K), R3.1, R4.1
unnamed: D8.1 (K), R5.1, R6.1
unnamed: D9.2 (A), J3.7, R3.2
unnamed: D9.1 (K), D10.1 (K), D13.1 (K), R7.2
unnamed: D11.1 (K), D12.1 (K), D14.1 (K), R8.2
unnamed: D11.2 (A), J3.9, R4.2
unnamed: D12.2 (A), J3.10, R6.2
unnamed: D10.2 (A), J3.8, R5.2

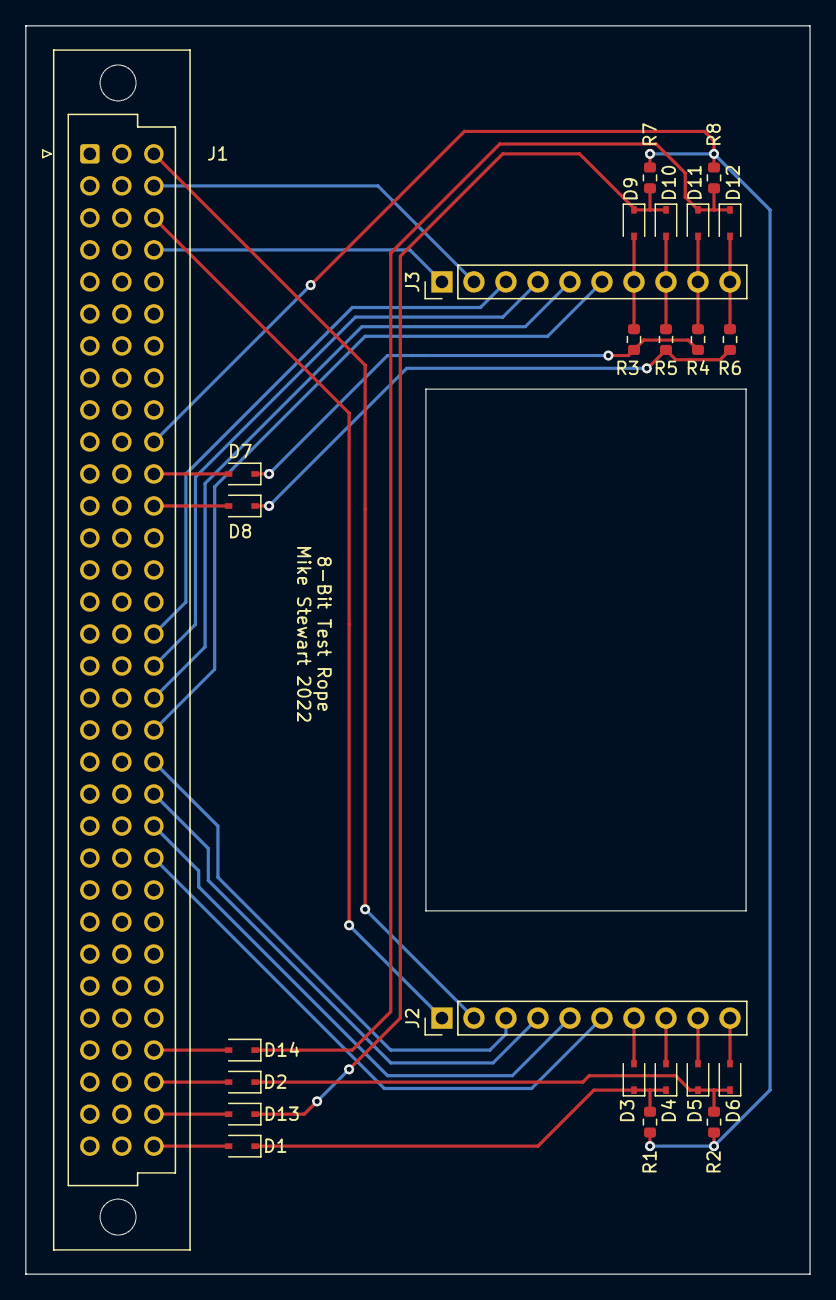
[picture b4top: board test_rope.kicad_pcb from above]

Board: 2 copper layers, 62.2 x 99.1 mm, 25 parts (0 on the bottom side), 33 nets.
